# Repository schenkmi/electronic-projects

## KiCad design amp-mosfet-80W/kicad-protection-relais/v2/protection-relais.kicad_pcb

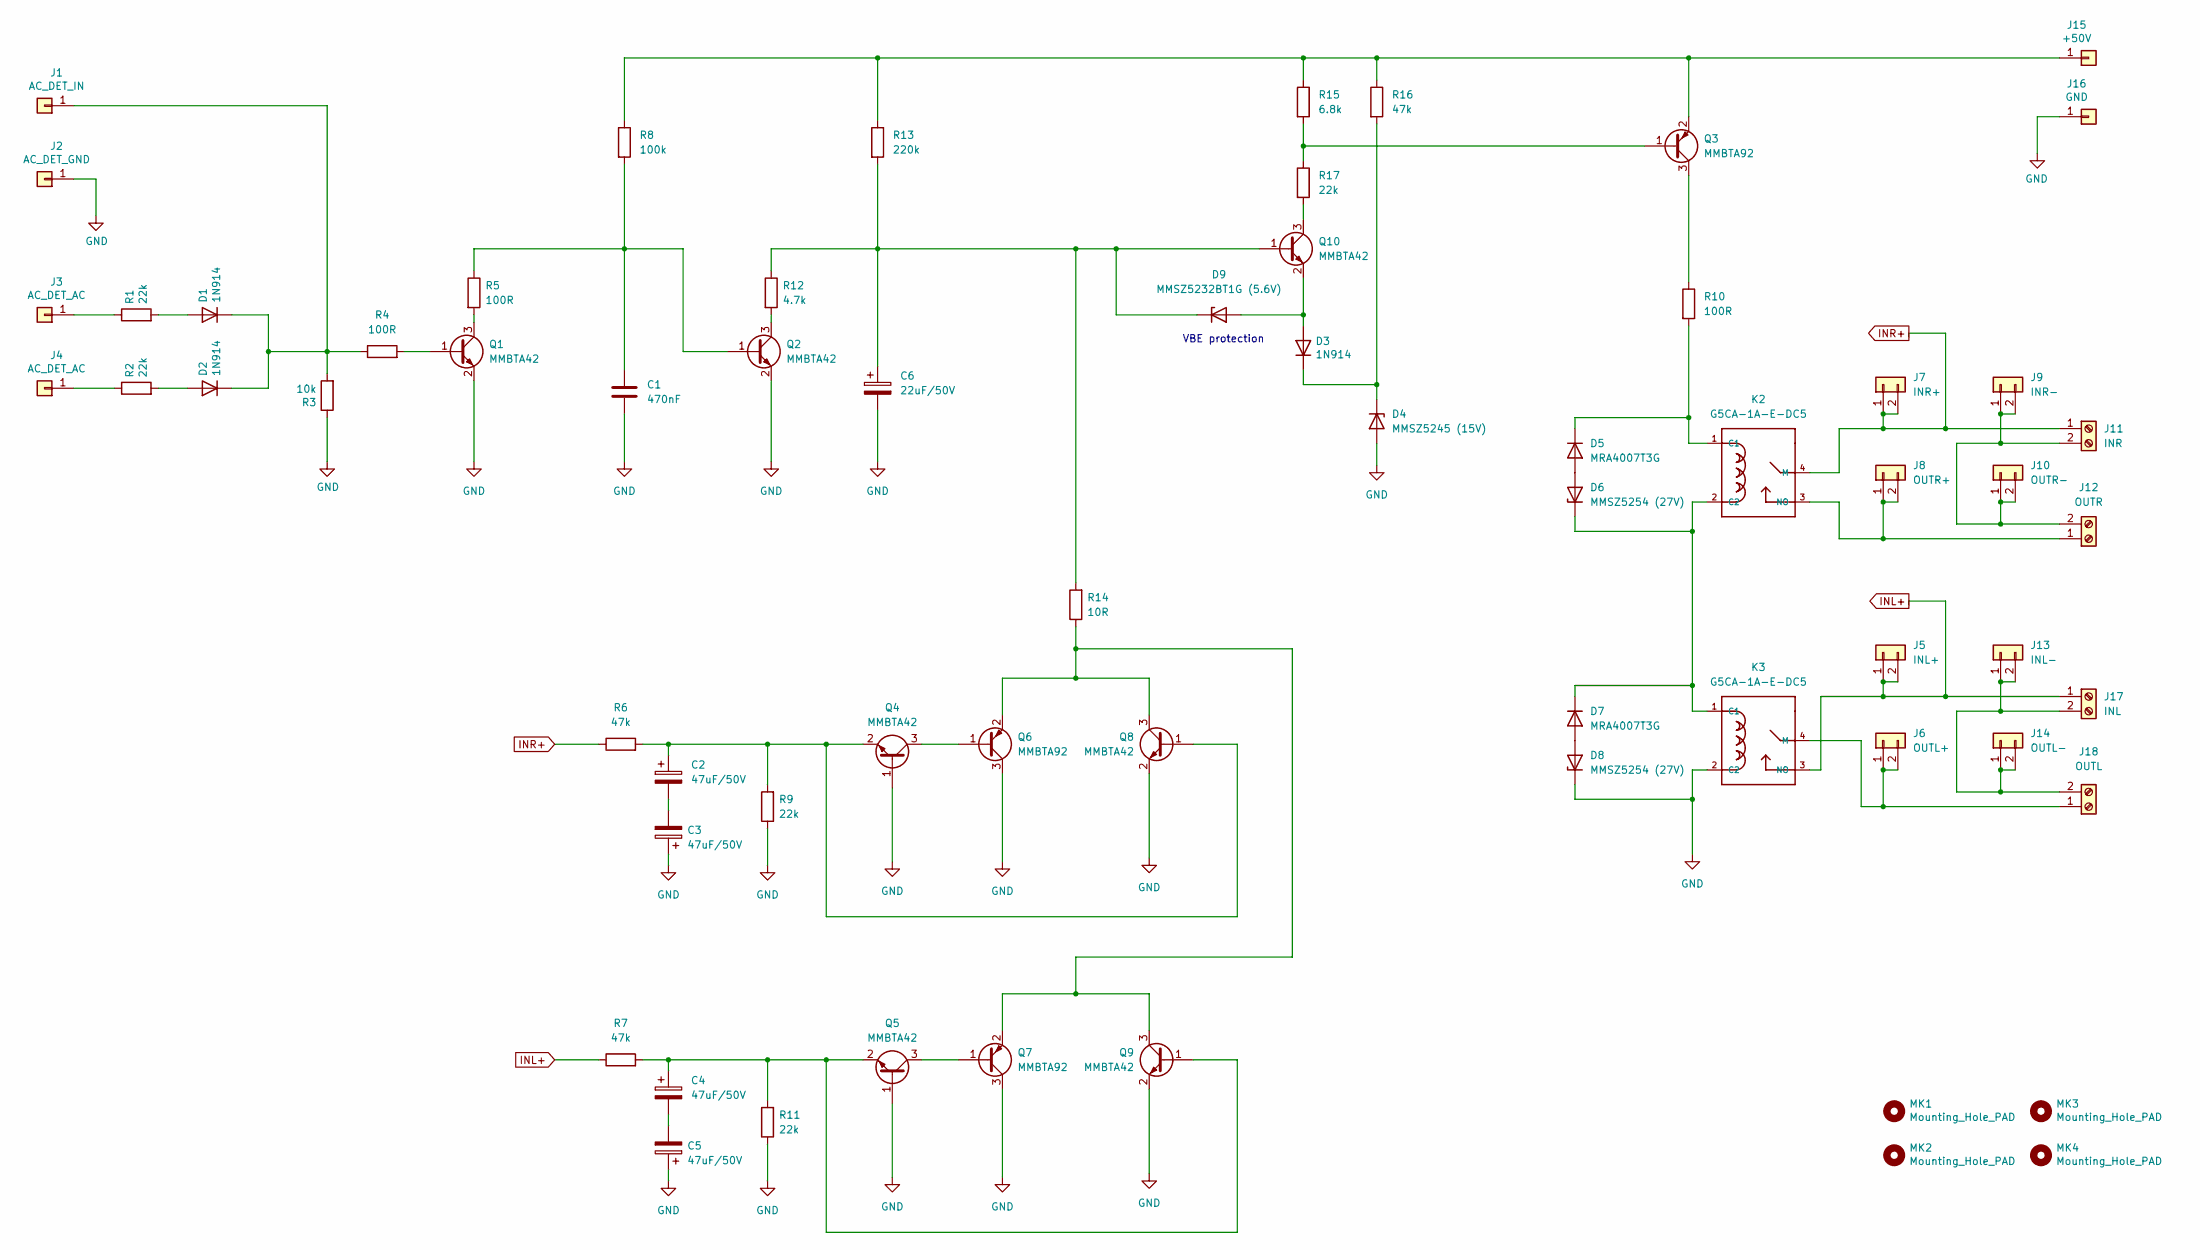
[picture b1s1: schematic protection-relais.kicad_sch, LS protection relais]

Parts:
C1: 470nF; C_1206_3216Metric_Pad1.33x1.80mm_HandSolder
C2, C3, C4, C5: 47uF/50V; CP_Radial_D6.3mm_P2.50mm
C6: 22uF/50V; CP_Radial_D5.0mm_P2.00mm
D1, D2, D3: 1N914; D_SOD-123
D4: MMSZ5245 (15V); D_SOD-123
D5, D7: MRA4007T3G; D_SMA
D6, D8: MMSZ5254 (27V); D_SOD-123
D9: MMSZ5232BT1G (5.6V); D_SOD-123
J1: AC_DET_IN; Pin_D1.0mm_L10.0mm
J2: AC_DET_GND; Pin_D1.0mm_L10.0mm
J3, J4: AC_DET_AC; Pin_D1.0mm_L10.0mm
J5: INL+; TE_62409-1
J6: OUTL+; TE_62409-1
J7: INR+; TE_62409-1
J8: OUTR+; TE_62409-1
J9: INR-; TE_62409-1
J10: OUTR-; TE_62409-1
J11: INR; TerminalBlock_RND_205-00012_1x02_P5.00mm_Horizontal
J12: OUTR; TerminalBlock_RND_205-00012_1x02_P5.00mm_Horizontal
J13: INL-; TE_62409-1
J14: OUTL-; TE_62409-1
J15: +50V; Pin_D1.0mm_L10.0mm
J16: GND; Pin_D1.0mm_L10.0mm
J17: INL; TerminalBlock_RND_205-00012_1x02_P5.00mm_Horizontal
J18: OUTL; TerminalBlock_RND_205-00012_1x02_P5.00mm_Horizontal
K2, K3: G5CA-1A-E-DC5; RELAY_G5CA-1A-E-DC5
MK1, MK2, MK3, MK4: Mounting_Hole_PAD; MountingHole_3.2mm_M3_Pad_Via
Q1, Q2, Q4, Q5, Q8, Q9, Q10: MMBTA42; SOT-23
Q3, Q6, Q7: MMBTA92; SOT-23
R1, R2, R9, R11, R17: 22k; R_0805_2012Metric_Pad1.20x1.40mm_HandSolder
R3: 10k; R_0805_2012Metric_Pad1.20x1.40mm_HandSolder
R4, R5, R10: 100R; R_0805_2012Metric_Pad1.20x1.40mm_HandSolder
R6, R7, R16: 47k; R_0805_2012Metric_Pad1.20x1.40mm_HandSolder
R8: 100k; R_0805_2012Metric_Pad1.20x1.40mm_HandSolder
R12: 4.7k; R_0805_2012Metric_Pad1.20x1.40mm_HandSolder
R13: 220k; R_0805_2012Metric_Pad1.20x1.40mm_HandSolder
R14: 10R; R_0805_2012Metric_Pad1.20x1.40mm_HandSolder
R15: 6.8k; R_0805_2012Metric_Pad1.20x1.40mm_HandSolder

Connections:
GND: C1.2, C3.1, C5.1, C6.2, D4.2 (A), D8.1 (K), J2.1, J16.1, K3.2 (C2), Q1.2 (E), Q2.2 (E), Q4.1 (B), Q5.1 (B), Q6.3 (C), Q7.3 (C), Q8.2 (E), Q9.2 (E), R3.1, R9.1, R11.1
INL+: J5.1, J5.2, J17.1, K3.3 (NO), R7.1
INR+: J7.1, J7.2, J11.1, K2.4 (M), R6.1
unnamed: C1.1, Q2.1 (B), R5.1, R8.2
unnamed: C2.1, Q4.2 (E), Q8.1 (B), R6.2, R9.2
unnamed: C2.2, C3.2
unnamed: C4.1, Q5.2 (E), Q9.1 (B), R7.2, R11.2
unnamed: C4.2, C5.2
unnamed: C6.1, D9.1 (K), Q10.1 (B), R12.1, R13.2, R14.2
unnamed: D1.1 (K), D2.1 (K), J1.1, R3.2, R4.1
unnamed: D1.2 (A), R1.2
unnamed: D2.2 (A), R2.2
unnamed: D5.1 (K), K2.1 (C1), R10.2
unnamed: D5.2 (A), D6.2 (A)
unnamed: D6.1 (K), D7.1 (K), K2.2 (C2), K3.1 (C1)
unnamed: D7.2 (A), D8.2 (A)
unnamed: J3.1, R1.1
unnamed: J4.1, R2.1
unnamed: J9.1, J9.2, J10.1, J10.2, J11.2, J12.2
unnamed: J8.1, J8.2, J12.1, K2.3 (NO)
unnamed: J13.1, J13.2, J14.1, J14.2, J17.2, J18.2
unnamed: J6.1, J6.2, J18.1, K3.4 (M)
unnamed: Q1.1 (B), R4.2
unnamed: Q1.3 (C), R5.2
unnamed: Q2.3 (C), R12.2
unnamed: Q3.1 (B), R15.2, R17.1
unnamed: Q4.3 (C), Q6.1 (B)
unnamed: Q5.3 (C), Q7.1 (B)
unnamed: Q6.2 (E), Q7.2 (E), Q8.3 (C), Q9.3 (C), R14.1
unnamed: D3.2 (A), D9.2 (A), Q10.2 (E)
unnamed: Q10.3 (C), R17.2
unnamed: Q3.3 (C), R10.1
unnamed: J15.1, Q3.2 (E), R8.1, R13.1, R15.1, R16.1
unnamed: D3.1 (K), D4.1 (K), R16.2

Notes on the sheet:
VBE protection

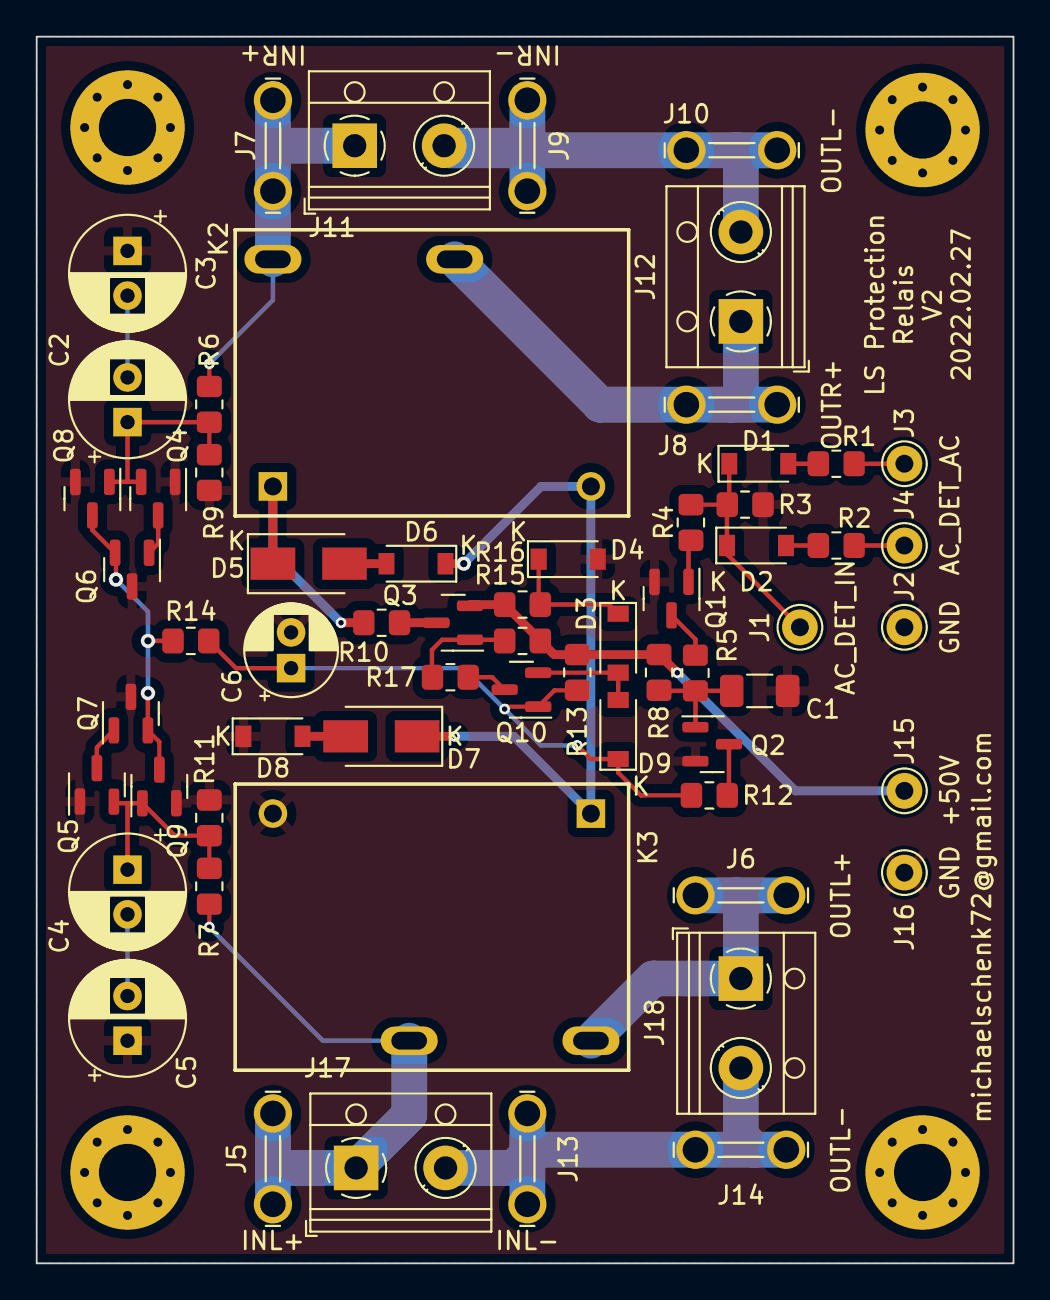
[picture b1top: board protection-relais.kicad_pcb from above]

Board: 2 copper layers, 54.6 x 68.6 mm, 66 parts (0 on the bottom side), 34 nets.
